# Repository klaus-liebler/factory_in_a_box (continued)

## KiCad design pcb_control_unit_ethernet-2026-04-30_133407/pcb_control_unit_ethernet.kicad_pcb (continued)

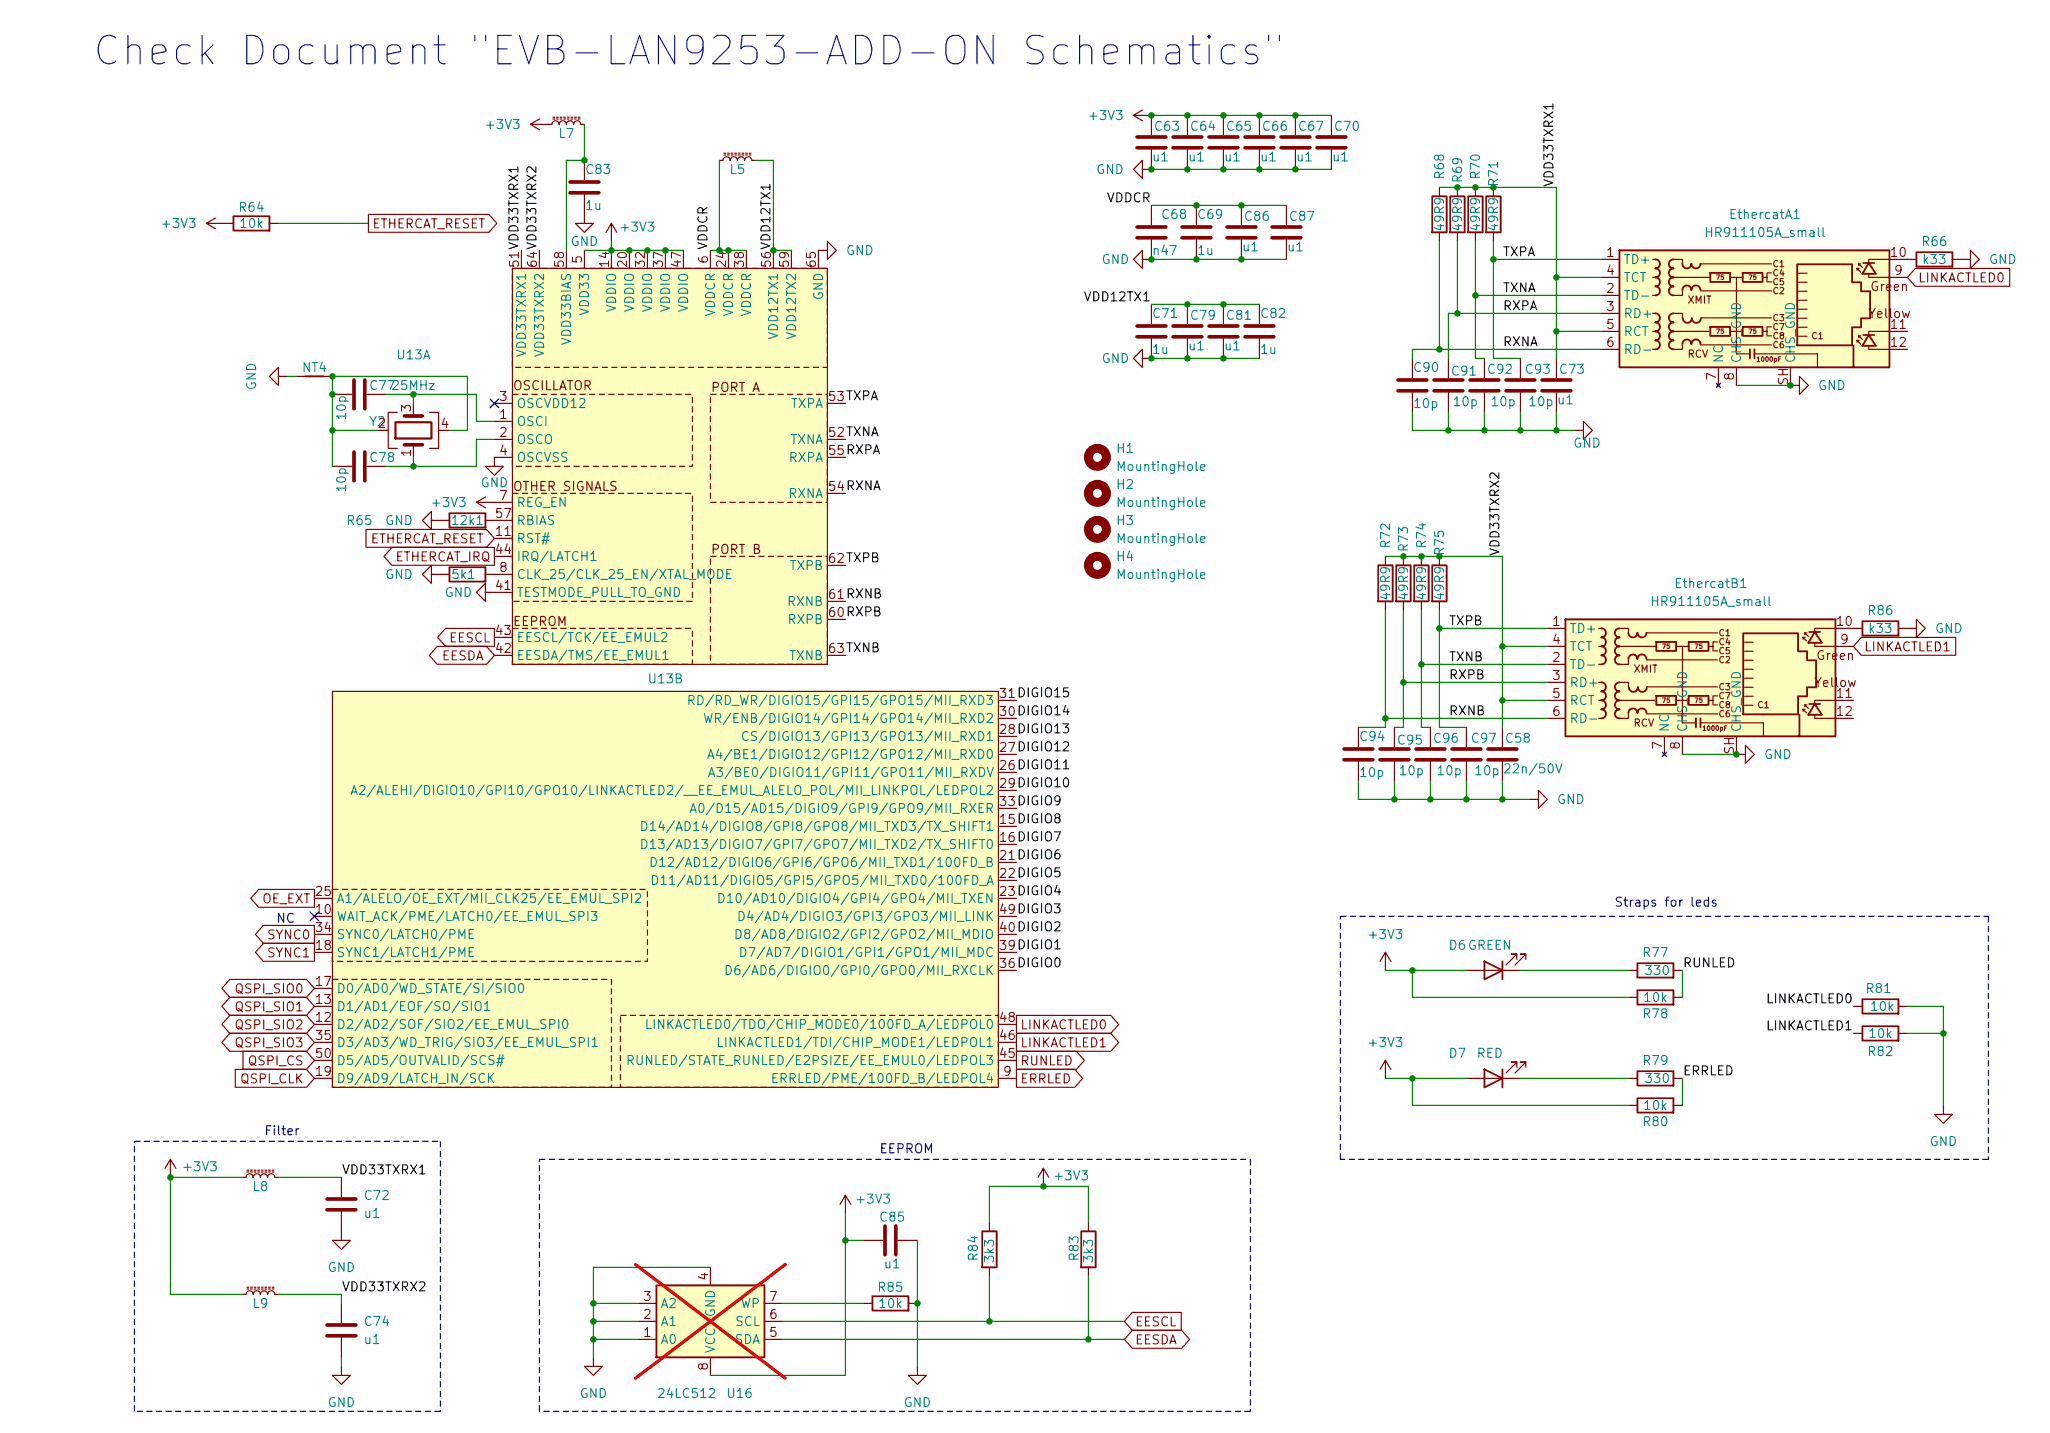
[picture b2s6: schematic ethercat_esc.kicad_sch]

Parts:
C58: 22n/50V; C_0402_1005Metric
C63, C64, C65, C66, C67, C70, C72, C73, C74, C79, C81, C85, C86, C87: u1; C_0402_1005Metric
C68: n47; C_0402_1005Metric
C69, C71, C82, C83: 1u; C_0402_1005Metric
C77, C78, C90, C91, C92, C93, C94, C95, C96, C97: 10p; C_0402_1005Metric
D6: GREEN; LED_1206_3216Metric_ReverseMount
D7: RED; LED_1206_3216Metric_ReverseMount
EthercatA1: HR911105A_small; RJ45_HANRUN_HR911105A
EthercatB1: HR911105A_small; RJ45_HANRUN_HR911105A
H1, H2, H3, H4: MountingHole; MountingHole_4.3mm_M4_DIN965
L5, L7, L8, L9: 220R@100M; L_0603_1608Metric
NT4: NetTie_2; NetTie-2_SMD_Pad0.5mm
R64, R78, R80, R81, R82, R85: 10k; R_0402_1005Metric
R65: 12k1; R_0402_1005Metric
R66, R86: k33; R_0402_1005Metric
R67: 5k1; R_0402_1005Metric
R68, R69, R70, R71, R72, R73, R74, R75: 49R9; R_0402_1005Metric
R77, R79: 330; R_0402_1005Metric
R83, R84: 3k3; R_0402_1005Metric
U13: QFN-64-1EP_9x9mm_P0.5mm_EP6x6mm_ThermalVias
U16: 24LC512; DIP-8_W7.62mm_Socket_LongPads; not fitted
Y2: 25MHz; Crystal_SMD_2016-4Pin_2.0x1.6mm

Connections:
+3V3: C63.1, C64.1, C65.1, C66.1, C67.1, C70.1, C85.1, D6.2 (A), D7.2 (A), L7.1, L8.1, L9.1, R64.1, R78.1, R80.1, R83.1, R84.1, U13.5 (VDD33), U13.7 (REG_EN), U13.14 (VDDIO), U13.20 (VDDIO), U13.32 (VDDIO), U13.37 (VDDIO), U13.47 (VDDIO), U16.8 (VCC); also elsewhere on the board
/EtherCAT/DIGIO0: U13.36 (D6/AD6/DIGIO0/GPI0/GPO0/MII_RXCLK)
/EtherCAT/DIGIO1: U13.39 (D7/AD7/DIGIO1/GPI1/GPO1/MII_MDC)
/EtherCAT/DIGIO2: U13.40 (D8/AD8/DIGIO2/GPI2/GPO2/MII_MDIO)
/EtherCAT/DIGIO3: U13.49 (D4/AD4/DIGIO3/GPI3/GPO3/MII_LINK)
/EtherCAT/DIGIO4: U13.23 (D10/AD10/DIGIO4/GPI4/GPO4/MII_TXEN)
/EtherCAT/DIGIO5: U13.22 (D11/AD11/DIGIO5/GPI5/GPO5/MII_TXD0/100F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)
/EtherCAT/DIGIO6: U13.21 (D12/AD12/DIGIO6/GPI6/GPO6/MII_TXD1/100F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)
/EtherCAT/DIGIO7: U13.16 (D13/AD13/DIGIO7/GPI7/GPO7/MII_TXD2/TX_S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)
/EtherCAT/DIGIO8: U13.15 (D14/AD14/DIGIO8/GPI8/GPO8/MII_TXD3/TX_S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)
/EtherCAT/DIGIO9: U13.33 (A0/D15/AD15/DIGIO9/GPI9/GPO9/MII_RXER)
/EtherCAT/DIGIO10: U13.29 (A2/ALEHI/DIGIO10/GPI10/GPO10/LINKACTLED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)
/EtherCAT/DIGIO11: U13.26 (A3/BE0/DIGIO11/GPI11/GPO11/MII_RXDV)
/EtherCAT/DIGIO12: U13.27 (A4/BE1/DIGIO12/GPI12/GPO12/MII_RXD0)
/EtherCAT/DIGIO13: U13.28 (CS/DIGIO13/GPI13/GPO13/MII_RXD1)
/EtherCAT/DIGIO14: U13.30 (WR/ENB/DIGIO14/GPI14/GPO14/MII_RXD2)
/EtherCAT/DIGIO15: U13.31 (RD/RD_WR/DIGIO15/GPI15/GPO15/MII_RXD3)
/EtherCAT/RXNA: C90.1, EthercatA1.6 (RD-), R68.2, U13.54 (RXNA)
/EtherCAT/RXNB: C94.1, EthercatB1.6 (RD-), R72.2, U13.61 (RXNB)
/EtherCAT/RXPA: C91.1, EthercatA1.3 (RD+), R69.2, U13.55 (RXPA)
/EtherCAT/RXPB: C95.1, EthercatB1.3 (RD+), R73.2, U13.60 (RXPB)
/EtherCAT/TXNA: C92.1, EthercatA1.2 (TD-), R70.2, U13.52 (TXNA)
/EtherCAT/TXNB: C96.1, EthercatB1.2 (TD-), R74.2, U13.63 (TXNB)
/EtherCAT/TXPA: C93.1, EthercatA1.1 (TD+), R71.2, U13.53 (TXPA)
/EtherCAT/TXPB: C97.1, EthercatB1.1 (TD+), R75.2, U13.62 (TXPB)
/EtherCAT/VDD12TX1: C71.1, C79.1, C81.1, C82.1, L5.2, U13.56 (VDD12TX1), U13.59 (VDD12TX2)
/EtherCAT/VDD33TXRX1: C72.1, C73.1, EthercatA1.4 (TCT), EthercatA1.5 (RCT), L8.2, R68.1, R69.1, R70.1, R71.1, U13.51 (VDD33TXRX1)
/EtherCAT/VDD33TXRX2: C58.1, C74.1, EthercatB1.4 (TCT), EthercatB1.5 (RCT), L9.2, R72.1, R73.1, R74.1, R75.1, U13.64 (VDD33TXRX2)
/EtherCAT/VDDCR: C68.1, C69.1, C86.1, C87.1, L5.1, U13.6 (VDDCR), U13.24 (VDDCR), U13.38 (VDDCR)
EESCL: R84.2, U13.43 (EESCL/TCK/EE_EMUL2), U16.6 (SCL)
EESDA: R83.2, U13.42 (EESDA/TMS/EE_EMUL1), U16.5 (SDA)
ERRLED: R79.2, R80.2, U13.9 (ERRLED/PME/100FD_B/LEDPOL4)
ETHERCAT_IRQ: U13.44 (IRQ/LATCH1); also elsewhere on the board
ETHERCAT_RESET: R64.2, U13.11 (RST#); also elsewhere on the board
GND: C58.2, C63.2, C64.2, C65.2, C66.2, C67.2, C68.2, C69.2, C70.2, C71.2, C72.2, C73.2, C74.2, C79.2, C81.2, C82.2, C83.2, C85.2, C86.2, C87.2, C90.2, C91.2, C92.2, C93.2, C94.2, C95.2, C96.2, C97.2, EthercatA1.8 (CHS_GND), EthercatA1.SH (CHS_GND), EthercatB1.8 (CHS_GND), EthercatB1.SH (CHS_GND), NT4.1, R65.1, R66.2, R67.1, R81.2, R82.2, R85.2, R86.2, U13.4 (OSCVSS), U13.41 (TESTMODE_PULL_TO_GND), U13.65 (GND), U16.1 (A0), U16.2 (A1), U16.3 (A2), U16.4 (GND); also elsewhere on the board
LINKACTLED0: EthercatA1.9, R81.1, U13.48 (LINKACTLED0/TDO/CHIP_MODE0/100FD_A/LEDP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)
LINKACTLED1: EthercatB1.9, R82.1, U13.46 (LINKACTLED1/TDI/CHIP_MODE1/LEDPOL1)
unnamed: C77.2, C78.2, NT4.2, Y2.2, Y2.4
unnamed: D6.1 (K), R77.1
unnamed: D7.1 (K), R79.1
unnamed: EthercatA1.10, R66.1
unnamed: EthercatB1.10, R86.1
unnamed: R67.2, U13.8 (CLK_25/CLK_25_EN/XTAL_MODE)
unnamed: C77.1, U13.1 (OSCI), Y2.3
unnamed: C78.1, U13.2 (OSCO), Y2.1
unnamed: R65.2, U13.57 (RBIAS)
unnamed: C83.1, L7.2, U13.58 (VDD33BIAS)
unnamed: R85.1, U16.7 (WP)
OE_EXT: U13.25 (A1/ALELO/OE_EXT/MII_CLK25/EE_EMUL_SPI2)
QSPI_CLK: U13.19 (D9/AD9/LATCH_IN/SCK); also elsewhere on the board
QSPI_CS: U13.50 (D5/AD5/OUTVALID/SCS#); also elsewhere on the board
QSPI_SIO0: U13.17 (D0/AD0/WD_STATE/SI/SIO0); also elsewhere on the board
QSPI_SIO1: U13.13 (D1/AD1/EOF/SO/SIO1); also elsewhere on the board
QSPI_SIO2: U13.12 (D2/AD2/SOF/SIO2/EE_EMUL_SPI0); also elsewhere on the board
QSPI_SIO3: U13.35 (D3/AD3/WD_TRIG/SIO3/EE_EMUL_SPI1); also elsewhere on the board
RUNLED: R77.2, R78.2, U13.45 (RUNLED/STATE_RUNLED/E2PSIZE/EE_EMUL0/LE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)
SYNC0: U13.34 (SYNC0/LATCH0/PME); also elsewhere on the board
SYNC1: U13.18 (SYNC1/LATCH1/PME); also elsewhere on the board

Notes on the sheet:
Straps for leds
Filter
Check Document "EVB-LAN9253-ADD-ON Schematics"
EEPROM

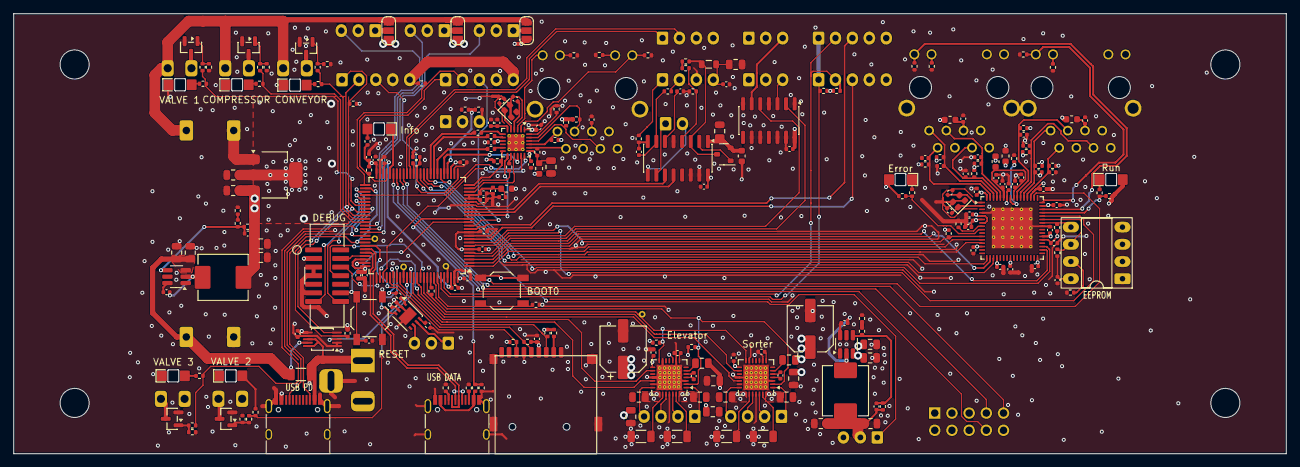
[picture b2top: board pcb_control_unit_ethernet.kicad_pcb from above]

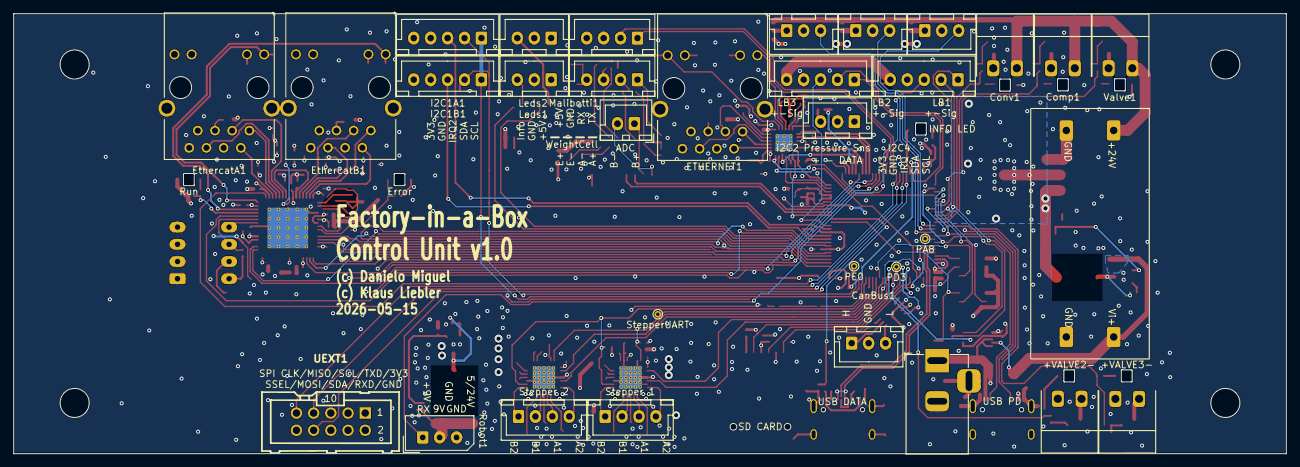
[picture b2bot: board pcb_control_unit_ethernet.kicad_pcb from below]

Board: 4 copper layers, 188.0 x 65.0 mm, 274 parts (32 on the bottom side), 207 nets.

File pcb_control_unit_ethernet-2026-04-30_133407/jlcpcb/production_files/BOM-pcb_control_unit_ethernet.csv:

Comment,Designator,Footprint,LCSC,Quantity
100uF,"C52,C53",CP_Elec_6.3x7.7,C72478,2
10k,"R1,R11,R12,R13,R14,R15,R2,R3,R33,R37,R38,R44,R46,R48,R51,R54,R56,R60,R61,R63,R64,R78,R80,R81,R82,R85,R89,R92,R95",R_0402_1005Metric,C25744,29
10n,"C18,C22,C23",C_0402_1005Metric,C5137480,3
10p,"C90,C91,C92,C93,C94,C95,C96,C97",C_0402_1005Metric,C106199,8
10p,"C77,C78",C_0402_1005Metric,C1574,2
10u,"C24,C33,C55,C60",C_0805_2012Metric,C6119889,4
10u/35V,"C28,C80",C_0805_2012Metric,C6119889,2
12k1,"R24,R65",R_0402_1005Metric,C25852,2
12uH,"L10,L3",L_Abracon_ASPI-0630LR,C177243,2
1k,"R10,R43,R45,R47,R49,R50,R52,R53,R55,R62,R90,R91,R93,R94",R_0402_1005Metric,C11702,14
1u,"C12,C15,C20,C69,C71,C82,C83",C_0402_1005Metric,C52923,7
220R@100M,L2,L_0603_1608Metric,C19330,1
220R@100M,"L1,L5,L6,L7,L8,L9",L_0603_1608Metric,C80165,6
22n/50V,"C45,C47,C58,C75",C_0402_1005Metric,C1532,4
22p,"C17,C19",C_0402_1005Metric,C1555,2
22u,"C31,C32,C34,C89,C98",C_0805_2012Metric,C45783,5
22u/35V,"C48,C49,C50,C51",C_0805_2012Metric,C6119901,4
25MHz,"Y1,Y2",Crystal_SMD_2016-4Pin_2.0x1.6mm,C19711739,2
2m,R34,R_1206_3216Metric,C844294,1
2u2,"C11,C13,C44,C46",C_0402_1005Metric,C12530,4
330,"R29,R30,R77,R79,R96",R_0402_1005Metric,C25104,5
33R,"R16,R17,R18,R76",R_0402_1005Metric,C25105,4
390m,"R39,R40,R41,R42",R_1206_3216Metric,C2907353,4
3k3,R31,R_0402_1005Metric,C140170,1
3k3,"R20,R83,R84",R_0402_1005Metric,C25879,3
3u3,L4,L_0805_2012Metric,C162585,1
49R9,"R25,R26,R27,R28,R68,R69,R70,R71,R72,R73,R74,R75",R_0402_1005Metric,C25120,12
4u7,C9,C_0402_1005Metric,C307423,1
56p,"C30,C88",C_0402_1005Metric,C107007,2
5k1,"R35,R36,R4,R5,R6,R67,R7,R8,R87,R9",R_0402_1005Metric,C25905,10
74AHCT125,U11,SOIC-14_3.9x8.7mm_P1.27mm,C155176,1
8k2,R59,R_0402_1005Metric,C137929,1
AMS1117-3.3,U5,SOT-223-3_TabPin2,C6186,1
Boot,SW2,SW_SPST_TL3342_smaller,C318884,1
Compressor,D4,LED_1206_3216Metric_ReverseMount,C2827254,1
GREEN,D6,LED_1206_3216Metric_ReverseMount,C2827254,1
HR911105A_small,"ETHERNET1,EthercatA1,EthercatB1",RJ45_HANRUN_HR911105A,C12074,3
HX711,U9,SOIC-16_3.9x9.9mm_P1.27mm,C6705483,1
INA226,U6,TSSOP-10_3x3mm_P0.5mm,C49851,1
IRLML6344,"Q1,Q2,Q3,Q5,Q6",SOT-23,C5271195,5
Info,D1,LED_1206_3216Metric_ReverseMount,C2827254,1
LAN8742A,U2,VQFN-24-1EP_4x4mm_P0.5mm_EP2.5x2.5mm_ThermalVias,C621425,1
M1,"R32,R88",R_0402_1005Metric,C25741,2
MMBT4403,Q4,SOT-23_smaller,C364313,1
Micro_SD_Card_Det1,J2,microSD push,C381082,1
Motor,D2,LED_1206_3216Metric_ReverseMount,C2827254,1
RED,D7,LED_1206_3216Metric_ReverseMount,C2827254,1
Reset,SW1,SW_SPST_TL3342_smaller,C318884,1
SIT3051TK,U10,DFN-8-1EP_3x3mm_P0.65mm_EP1.55x2.4mm,C601078,1
STDC14,J1,IDC-Header_2x07_P1.27mm_Vertical_SMD,C6332251,1
STM32H563VITx,U1,LQFP-100_14x14mm_P0.5mm,C6937834,1
TMC2209,"U7,U8",QFN-28-1EP_5x5mm_P0.5mm_EP3.75x3.75mm_ThermalVias,C2150710,2
TPS54202DDC,U4,SOT-23-6_Handsoldering,C191884,1
USB STM32,"J5,J6",USB_C_Receptacle_HRO_TYPE-C-31-M-12_smaller,C165948,2
Valve,"D3,D5,D8",LED_1206_3216Metric_ReverseMount,C2827254,3
k1,"R57,R58",R_0402_1005Metric,C25076,2
k33,"R66,R86",R_0402_1005Metric,C25104,2
n47,"C21,C68",C_0402_1005Metric,C76971,2
u1,"C1,C10,C14,C16,C2,C3,C35,C38,C39,C4,C5,C54,C56,C57,C59,C6,C61,C62,C63,C64,C65,C66,C67,C7,C70,C72,C73,C74,C79,C8,C81,C85,C86,C87",C_0402_1005Metric,C1525,34
u1/16V,"C29,C84",C_0402_1005Metric,C1525,2
u1/35V,"C27,C40,C41,C42,C43,C76",C_0805_2012Metric,C49678,6
u1/50V,"C36,C37",C_0805_2012Metric,C49678,2
~,U13,QFN-64-1EP_9x9mm_P0.5mm_EP6x6mm_ThermalVias,C5745149,1
StepperUART,TP1,TestPoint_THTPad_D1.0mm_Drill0.5mm,,1
LightBarrier3,LB3,JST_XH_B3B-XH-A_1x03_P2.50mm_Vertical_smaller,,1
TOF3,I2C4,JST_XH_B5B-XH-A_1x05_P2.50mm_Vertical_smaller,,1
Valve,J30,"PhoenixContact_MC_1,5_2-G-3.5_1x02_P3.50mm_Horizontal_smallerCourtyard",,1
Valve,Valve2,"PhoenixContact_MC_1,5_2-G-3.5_1x02_P3.50mm_Horizontal_smallerCourtyard",,1
TOF2,I2C2,JST_XH_B5B-XH-A_1x05_P2.50mm_Vertical_smaller,,1
WS2812_CH1,Leds1,JST_XH_B3B-XH-A_1x03_P2.50mm_Vertical_smaller,,1
WS2812_CH2,Leds2,JST_XH_B3B-XH-A_1x03_P2.50mm_Vertical_smaller,,1
MT3608,X1,DCDC_MT3608,,1
LightBarrier2,LB2,JST_XH_B3B-XH-A_1x03_P2.50mm_Vertical_smaller,,1
LightBarrier1,LB1,JST_XH_B3B-XH-A_1x03_P2.50mm_Vertical_smaller,,1
INB,J3,JST_XH_B2B-XH-A_1x02_P2.50mm_Vertical,,1
RGB,I2C1A1,JST_XH_B5B-XH-A_1x05_P2.50mm_Vertical_smaller,,1
TOF1,I2C1B1,JST_XH_B5B-XH-A_1x05_P2.50mm_Vertical_smaller,,1
Weight,J23,JST_XH_B4B-XH-A_1x04_P2.50mm_Vertical_smaller,,1
BH10S,UEXT1,UEXTM-PTH,,1
CAN,CanBus1,JST_XH_B3B-XH-A_1x03_P2.50mm_Vertical_smaller,,1
Conveyor,Conv1,"PhoenixContact_MC_1,5_2-G-3.5_1x02_P3.50mm_Horizontal_smallerCourtyard",,1
STEP1,J17,JST_XH_B4B-XH-A_1x04_P2.50mm_Vertical_smaller,,1
Bus-Servo,Robot1,Molex_SPOX_5267-03A_1x03_P2.50mm_Vertical,,1
DC IN,J4,BarrelJack_Horizontal,,1
Compressor,Comp1,"PhoenixContact_MC_1,5_2-G-3.5_1x02_P3.50mm_Horizontal_smallerCourtyard",,1
STEP2,J18,JST_XH_B4B-XH-A_1x04_P2.50mm_Vertical_smaller,,1
Valve,Valve1,"PhoenixContact_MC_1,5_2-G-3.5_1x02_P3.50mm_Horizontal_smallerCourtyard",,1
Malibotti,Malibotti1,JST_XH_B4B-XH-A_1x04_P2.50mm_Vertical_smaller,,1
PressureTransducer,Pressure1,JST_XH_B3B-XH-A_1x03_P2.50mm_Vertical_smaller,,1
PE0,TP5,TestPoint_THTPad_D1.0mm_Drill0.5mm,,1
PD3,TP4,TestPoint_THTPad_D1.0mm_Drill0.5mm,,1
PA8,TP3,TestPoint_THTPad_D1.0mm_Drill0.5mm,,1
TPS54202DDC,U12,SOT-23-6_Handsoldering,,1

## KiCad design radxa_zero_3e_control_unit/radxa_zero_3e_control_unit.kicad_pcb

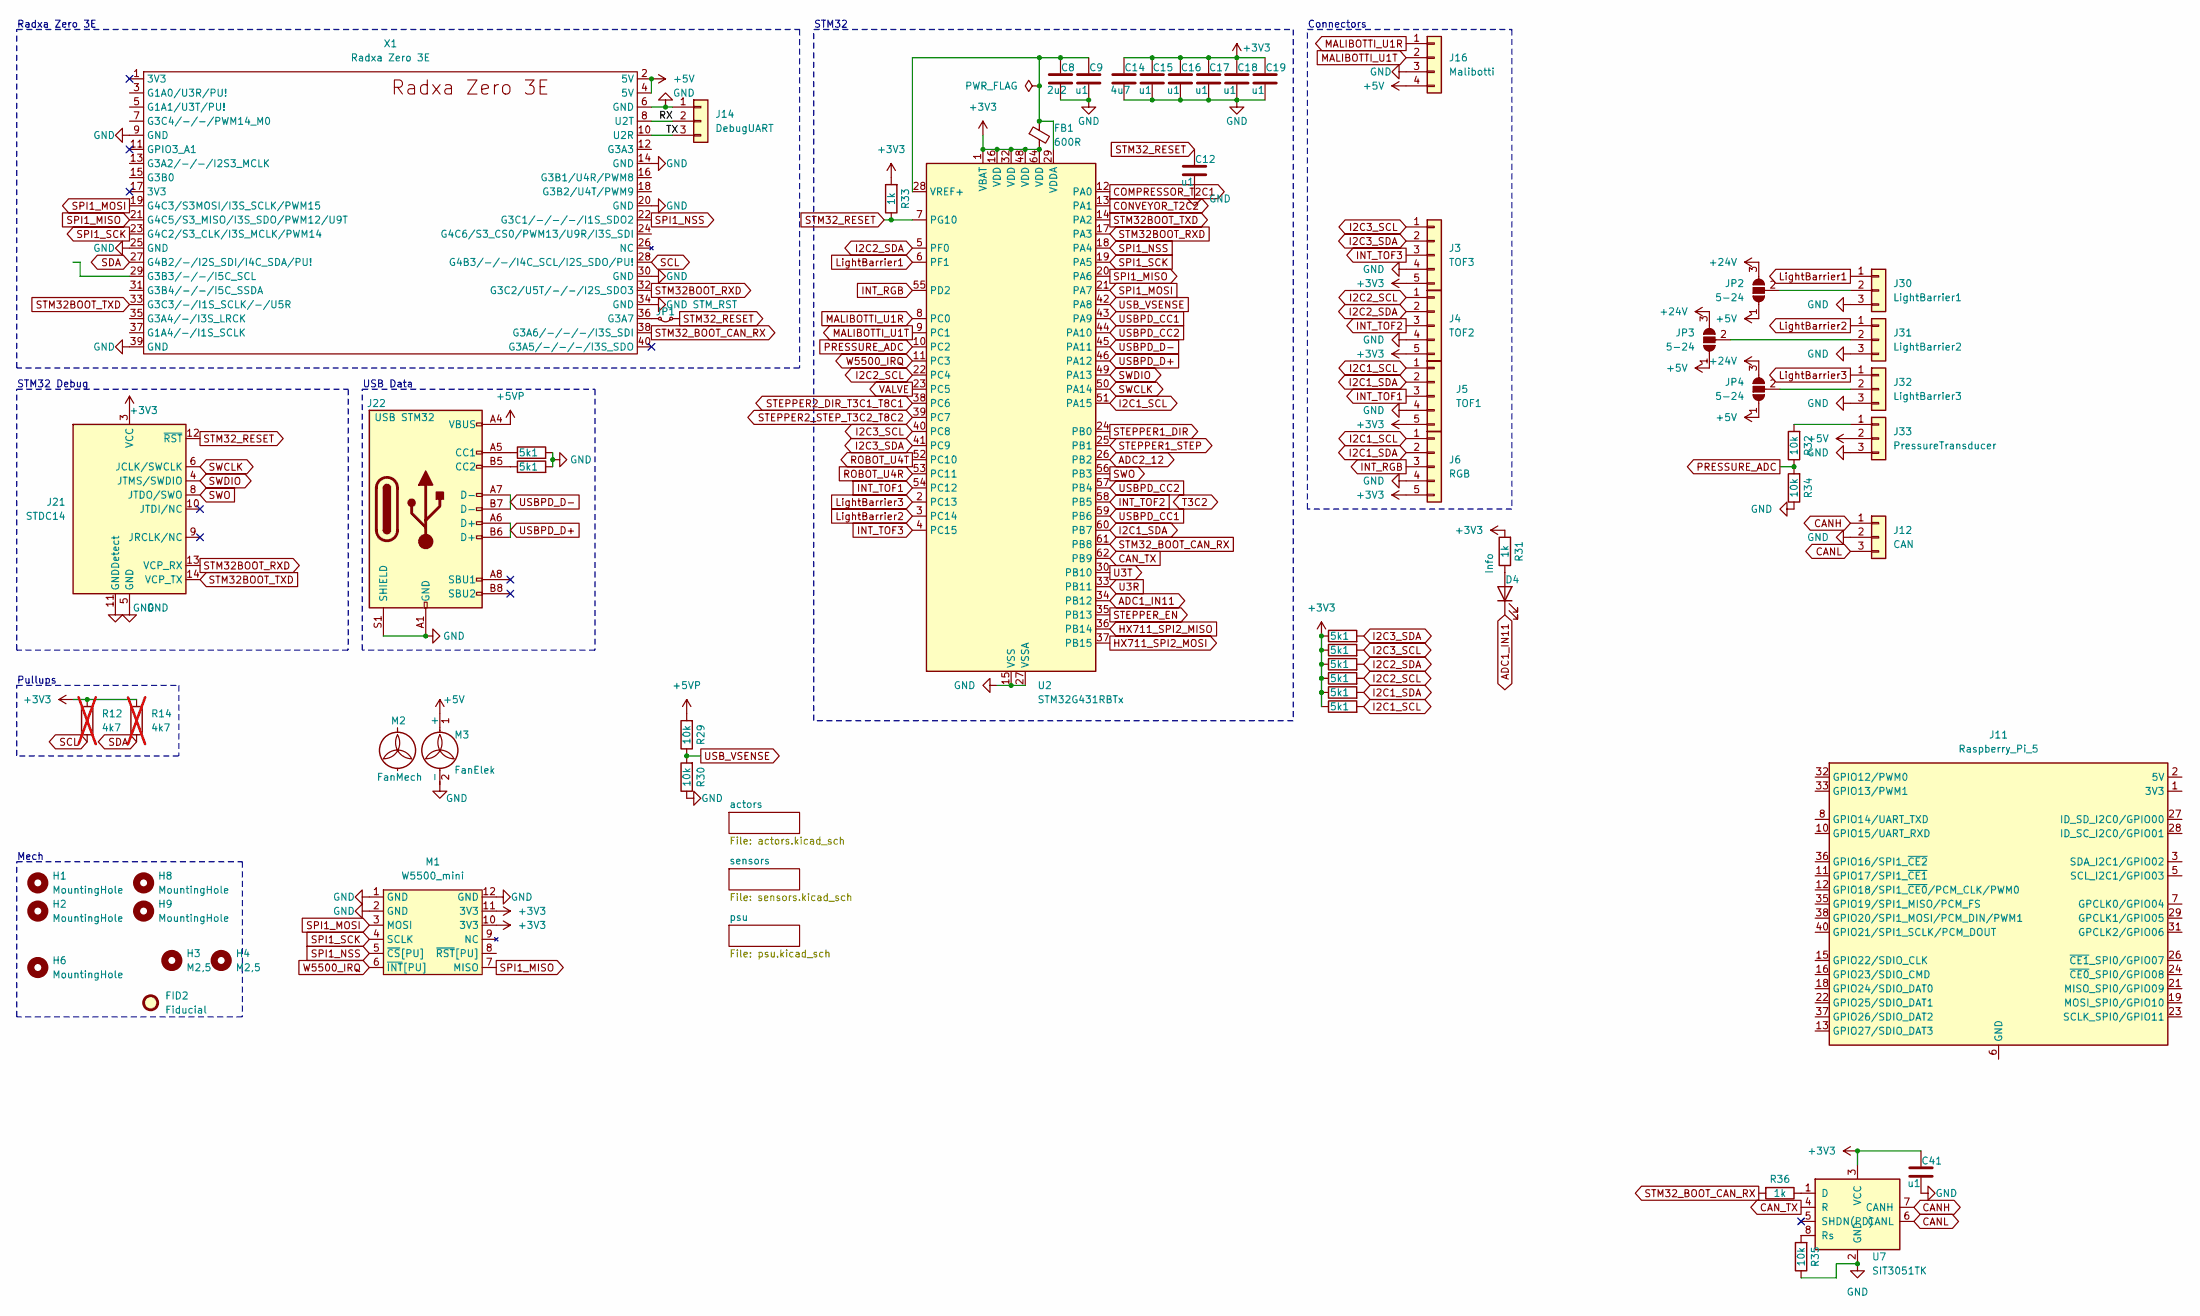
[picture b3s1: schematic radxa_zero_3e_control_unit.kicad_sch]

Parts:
C8: 2u2; C_0402_1005Metric; MPN CL05A105KA5NQNC
C9, C12, C15, C16, C17, C18, C19, C41: u1; C_0402_1005Metric; MPN GRM033R61A104KE15D
C14: 4u7; C_0402_1005Metric; MPN CL05A475MP5NRNC
D4: Info; LED_1206_3216Metric_ReverseMount; MPN LTST-C230KRKT
FB1: 600R; L_0603_1608Metric; MPN BLM18AG601SN1D
FID2: Fiducial; barrel_jack_positive_polarity
H1, H2, H8, H9: MountingHole; MountingHole_4.3mm_M4
H3, H4: M2,5; MountingHole_2.7mm
H6: MountingHole; MountingHole_2.7mm
J3: TOF3; JST_XH_B5B-XH-A_1x05_P2.50mm_Vertical_smaller
J4: TOF2; JST_XH_B5B-XH-A_1x05_P2.50mm_Vertical_smaller
J5: TOF1; JST_XH_B5B-XH-A_1x05_P2.50mm_Vertical_smaller
J6: RGB; JST_XH_B5B-XH-A_1x05_P2.50mm_Vertical_smaller
J11: Raspberry_Pi_5; RasPi5
J12: CAN; JST_XH_B3B-XH-A_1x03_P2.50mm_Vertical_smaller
J14: DebugUART; PinHeader_1x03_P2.54mm_Vertical_smallerCourtyard
J16: Malibotti; JST_XH_B4B-XH-A_1x04_P2.50mm_Vertical_smaller
J21: STDC14; IDC_2x07_P1.27mm_Vertical
J22: USB STM32; USB_C_Receptacle_HRO_TYPE-C-31-M-12_smaller; MPN TYPE-C-31-M-12
J30: LightBarrier1; JST_XH_B3B-XH-A_1x03_P2.50mm_Vertical_smaller
J31: LightBarrier2; JST_XH_B3B-XH-A_1x03_P2.50mm_Vertical_smaller
J32: LightBarrier3; JST_XH_B3B-XH-A_1x03_P2.50mm_Vertical_smaller
J33: PressureTransducer; JST_XH_B3B-XH-A_1x03_P2.50mm_Vertical_smaller
JP1: STM_RST; SolderJumper-2_P1.3mm_Bridged2Bar_RoundedPad1.0x1.5mm
JP2, JP3, JP4: 5-24; SolderJumper-3_P1.3mm_Open_RoundedPad1.0x1.5mm_NumberLabels
M1: W5500_mini; W5500-mini
M2: FanMech; FAN2507
M3: FanElek; JST_XH_B2B-XH-A_1x02_P2.50mm_Vertical
R12, R14: 4k7; R_0201_0603Metric; not fitted
R13, R28, R38, R39, R40, R41, R42, R43: 5k1; R_0201_0603Metric
R29, R30: 10k; R_0201_0603Metric; MPN 0201WMF1002TEE
R31, R33, R36: 1k; R_0402_1005Metric; MPN 0402WGF1001TCE
R32, R34, R35: 10k; R_0402_1005Metric; MPN 0201WMF1002TEE
U2: STM32G431RBTx; LQFP-64_10x10mm_P0.5mm
U7: SIT3051TK; DFN-8-1EP_3x3mm_P0.65mm_EP1.55x2.4mm
X1: Radxa Zero 3E

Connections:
+3V3: C14.1, C15.1, C16.1, C17.1, C18.1, C19.1, C41.1, FB1.2, J3.5, J4.5, J5.5, J6.5, J21.3 (VCC), M1.10 (3V3), M1.11 (3V3), R12.1, R14.1, R31.2, R33.2, R38.1, R39.1, R40.1, R41.1, R42.1, R43.1, U2.1 (VBAT), U2.16 (VDD), U2.32 (VDD), U2.48 (VDD), U2.64 (VDD), U7.3 (VCC); also elsewhere on the board
+5V: J16.4, J33.2, JP2.1 (A), JP3.1 (A), JP4.1 (A), M3.1 (+), X1.2 (5V), X1.4 (5V); also elsewhere on the board
+5VP: J22.A4 (VBUS), J22.A9 (VBUS), J22.B4 (VBUS), J22.B9 (VBUS), R29.2
+24V: JP2.3 (B), JP3.3 (B), JP4.3 (B); also elsewhere on the board
/RX: J14.2, X1.8 (U2T)
/TX: J14.3, X1.10 (U2R)
ADC1_IN11: D4.1 (K), U2.34 (PB12)
ADC2_12: U2.26 (PB2)
CANH: J12.1, U7.7 (CANH)
CANL: J12.3, U7.6 (CANL)
CAN_TX: U2.62 (PB9), U7.4 (R)
COMPRESSOR_T2C1: U2.12 (PA0); also elsewhere on the board
CONVEYOR_T2C2: U2.13 (PA1); also elsewhere on the board
GND: C8.2, C9.2, C12.2, C14.2, C15.2, C16.2, C17.2, C18.2, C19.2, C41.2, J3.4, J4.4, J5.4, J6.4, J12.2, J14.1, J16.3, J21.5 (GND), J21.7 (GND), J21.11 (GNDDetect), J22.A1 (GND), J22.A12 (GND), J22.B1 (GND), J22.B12 (GND), J22.S1 (SHIELD), J30.3, J31.3, J32.3, J33.3, M1.1 (GND), M1.2 (GND), M1.12 (GND), M3.2 (-), R13.2, R28.2, R30.1, R34.1, R35.1, U2.15 (VSS), U2.27 (VSSA), U2.31 (VSS), U2.47 (VSS), U2.63 (VSS), U7.2 (GND), U7.9 (PAD), X1.6 (GND), X1.9 (GND), X1.14 (GND), X1.20 (GND), X1.25 (GND), X1.30 (GND), X1.34 (GND), X1.39 (GND); also elsewhere on the board
HX711_SPI2_MISO: U2.36 (PB14); also elsewhere on the board
HX711_SPI2_MOSI: U2.37 (PB15); also elsewhere on the board
I2C1_SCL: J5.1, J6.1, R43.2, U2.51 (PA15)
I2C1_SDA: J5.2, J6.2, R42.2, U2.60 (PB7)
I2C2_SCL: J4.1, R41.2, U2.22 (PC4)
I2C2_SDA: J4.2, R40.2, U2.5 (PF0)
I2C3_SCL: J3.1, R39.2, U2.40 (PC8); also elsewhere on the board
I2C3_SDA: J3.2, R38.2, U2.41 (PC9); also elsewhere on the board
INT_RGB: J6.3, U2.55 (PD2)
INT_TOF1: J5.3, U2.54 (PC12)
INT_TOF2: J4.3, U2.58 (PB5)
INT_TOF3: J3.3, U2.4 (PC15)
LightBarrier1: J30.1, U2.6 (PF1)
LightBarrier2: J31.1, U2.3 (PC14)
LightBarrier3: J32.1, U2.2 (PC13)
MALIBOTTI_U1R: J16.1, U2.8 (PC0)
MALIBOTTI_U1T: J16.2, U2.9 (PC1)
unnamed: D4.2 (A), R31.1
unnamed: J11.1 (3V3), J11.17 (3V3)
unnamed: J11.2 (5V), J11.4 (5V)
unnamed: J11.6 (GND), J11.9 (GND), J11.14 (GND), J11.20 (GND), J11.25 (GND), J11.30 (GND), J11.34 (GND), J11.39 (GND)
unnamed: J22.A5 (CC1), R13.1
unnamed: J22.B5 (CC2), R28.1
unnamed: J30.2, JP2.2 (C)
unnamed: J31.2, JP3.2 (C)
unnamed: J32.2, JP4.2 (C)
unnamed: J33.1, R32.2
unnamed: JP1.2 (B), X1.36 (G3A7)
unnamed: C8.1, C9.1, FB1.1, U2.28 (VREF+), U2.29 (VDDA)
unnamed: R36.1, U7.1 (D)
unnamed: R35.2, U7.8 (Rs)
PRESSURE_ADC: R32.1, R34.2, U2.10 (PC2)
ROBOT_U4R: U2.53 (PC11); also elsewhere on the board
ROBOT_U4T: U2.52 (PC10); also elsewhere on the board
SCL: R12.2, X1.28 (G4B3/-/-/I4C_SCL/I2S_SDO/PU!)
SDA: R14.2, X1.27 (G4B2/-/I2S_SDI/I4C_SDA/PU!)
SPI1_MISO: M1.7 (MISO), U2.20 (PA6), X1.21 (G4C5/S3_MISO/I3S_SDO/PWM12/U9T)
SPI1_MOSI: M1.3 (MOSI), U2.21 (PA7), X1.19 (G4C3/S3MOSI/I3S_SCLK/PWM15)
SPI1_NSS: M1.5 (~CS[PU]), U2.18 (PA4), X1.22 (G3C1/-/-/-/I1S_SDO2)
SPI1_SCK: M1.4 (SCLK), U2.19 (PA5), X1.23 (G4C2/S3_CLK/I3S_MCLK/PWM14)
STEPPER1_DIR: U2.24 (PB0); also elsewhere on the board
STEPPER1_STEP: U2.25 (PB1); also elsewhere on the board
STEPPER2_DIR_T3C1_T8C1: U2.38 (PC6); also elsewhere on the board
STEPPER2_STEP_T3C2_T8C2: U2.39 (PC7); also elsewhere on the board
STEPPER_EN: U2.35 (PB13); also elsewhere on the board
STEPPER_UART: U2.33 (PB11); also elsewhere on the board
STM32BOOT_RXD: J21.13 (VCP_RX), U2.17 (PA3), X1.32 (G3C2/U5T/-/-/I2S_SDO3)
STM32BOOT_TXD: J21.14 (VCP_TX), U2.14 (PA2), X1.33 (G3C3/-/I1S_SCLK/-/U5R)
STM32_BOOT_CAN_RX: R36.2, U2.61 (PB8), X1.38 (G3A6/-/-/-/I3S_SDI)
STM32_RESET: C12.1, J21.12 (~RST), JP1.1 (A), R33.1, U2.7 (PG10)
SWCLK: J21.6 (JCLK/SWCLK), U2.50 (PA14)
SWDIO: J21.4 (JTMS/SWDIO), U2.49 (PA13)
SWO: J21.8 (JTDO/SWO), U2.56 (PB3)
U3T: U2.30 (PB10); also elsewhere on the board
USBPD_CC1: U2.43 (PA9), U2.59 (PB6); also elsewhere on the board
USBPD_CC2: U2.44 (PA10), U2.57 (PB4); also elsewhere on the board
USBPD_D+: J22.A6 (D+), J22.B6 (D+), U2.46 (PA12)
USBPD_D-: J22.A7 (D-), J22.B7 (D-), U2.45 (PA11)
USB_VSENSE: R29.1, R30.2, U2.42 (PA8)
VALVE: U2.23 (PC5); also elsewhere on the board
W5500_IRQ: M1.6 (~INT[PU]), U2.11 (PC3)

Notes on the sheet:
Mech
STM32 Debug
Connectors
Pullups
STM32
Radxa Zero 3E
USB Data

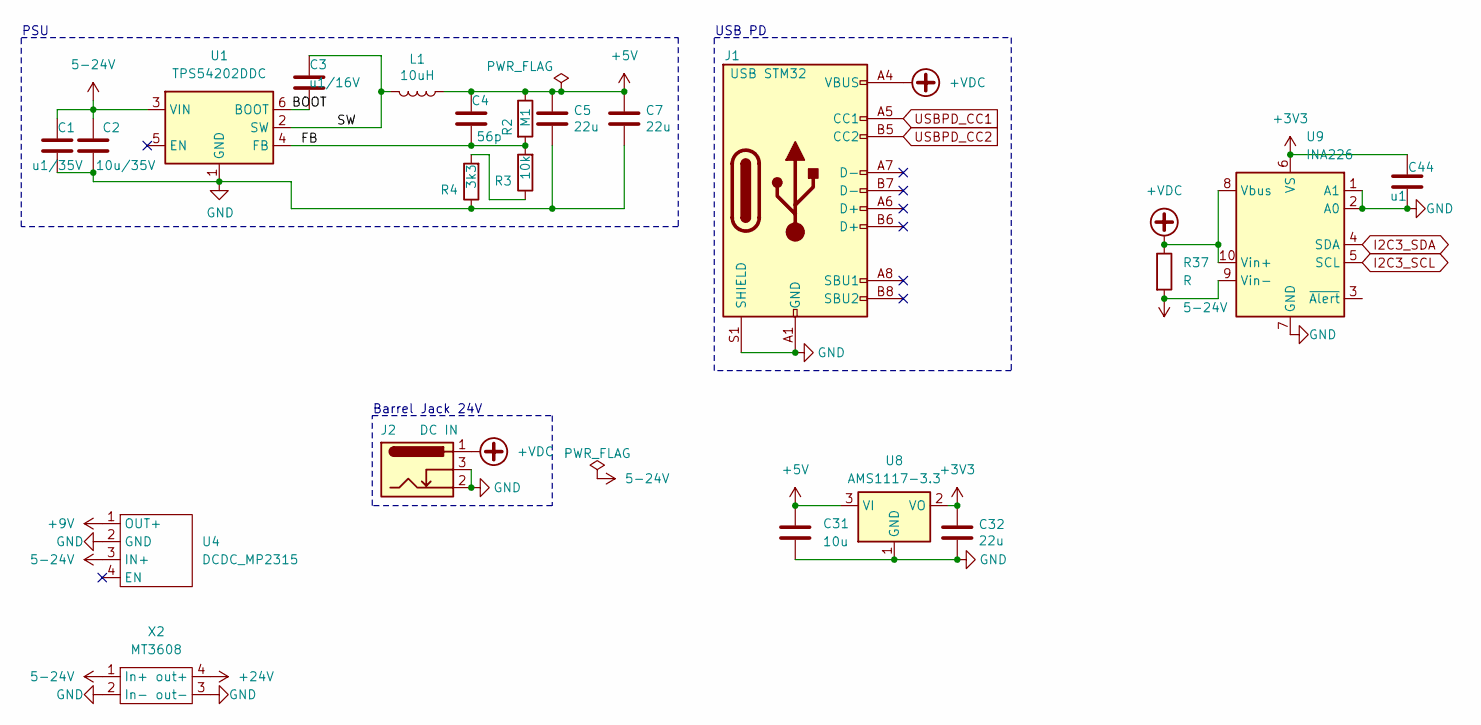
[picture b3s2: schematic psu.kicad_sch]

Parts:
C1: u1/35V; C_0603_1608Metric; MPN CC0603KRX7R9BB104
C2: 10u/35V; C_0805_2012Metric; MPN CGA0805X5R106K350MT
C3: u1/16V; C_0603_1608Metric; MPN CC0603KRX7R9BB104
C4: 56p; C_0402_1005Metric; MPN CC0402JRNPO9BN560
C5, C7, C32: 22u; C_0805_2012Metric; MPN CL10A226MP8NUNE
C31: 10u; C_0805_2012Metric
C44: u1; C_0402_1005Metric; MPN GRM033R61A104KE15D
J1: USB STM32; USB_C_Receptacle_HRO_TYPE-C-31-M-12_smaller; MPN TYPE-C-31-M-12
J2: DC IN; BarrelJack_Horizontal; MPN DC-005 2.0
L1: 10uH; L_Abracon_ASPI-0630LR; MPN FXL0630-100-M
R2: M1; R_0402_1005Metric; MPN 0201WMF1003TEE
R3: 10k; R_0402_1005Metric; MPN 0201WMF1002TEE
R4: 3k3; R_0402_1005Metric; MPN 0402WGF3301TCE
R37: R; R_2010_5025Metric
U1: TPS54202DDC; SOT-23-6_Handsoldering; MPN TPS54202DDCR
U4: DCDC_MP2315
U8: AMS1117-3.3; SOT-223-3_TabPin2
U9: INA226; VSSOP-10_3x3mm_P0.5mm
X2: MT3608; DCDC_MT3608

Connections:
5-24V: C1.2, C2.2, R37.2, U1.3 (VIN), U4.3 (IN+), U9.9 (Vin-), X2.1 (In+); also elsewhere on the board
+3V3: C32.1, C44.1, U8.2 (VO), U9.6 (VS); also elsewhere on the board
+5V: C4.2, C5.1, C7.1, C31.1, L1.1, R2.1, U8.3 (VI); also elsewhere on the board
+9V: U4.1 (OUT+); also elsewhere on the board
+24V: X2.4 (out+); also elsewhere on the board
+VDC: J1.A4 (VBUS), J1.A9 (VBUS), J1.B4 (VBUS), J1.B9 (VBUS), J2.1, R37.1, U9.8 (Vbus), U9.10 (Vin+)
/psu/BOOT: C3.1, U1.6 (BOOT)
/psu/FB: C4.1, R2.2, R3.2, U1.4 (FB)
/psu/SW: C3.2, L1.2, U1.2 (SW)
GND: C1.1, C2.1, C5.2, C7.2, C31.2, C32.2, C44.2, J1.A1 (GND), J1.A12 (GND), J1.B1 (GND), J1.B12 (GND), J1.S1 (SHIELD), J2.2, J2.3, R4.1, U1.1 (GND), U4.2 (GND), U8.1 (GND), U9.1 (A1), U9.2 (A0), U9.7 (GND), X2.2 (In-), X2.3 (out-); also elsewhere on the board
I2C3_SCL: U9.5 (SCL); also elsewhere on the board
I2C3_SDA: U9.4 (SDA); also elsewhere on the board
unnamed: R3.1, R4.2
USBPD_CC1: J1.A5 (CC1); also elsewhere on the board
USBPD_CC2: J1.B5 (CC2); also elsewhere on the board

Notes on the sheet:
PSU
Barrel Jack 24V
USB PD
